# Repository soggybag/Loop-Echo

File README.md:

# Loop Echo (working name)

A single-PT2399 delay with an **effects loop in the feedback path**:
- only the repeats circulate through the loop;
- the first echo is clean, and each later echo goes through the external effect again: fuzz degrades, a filter re-voices, a pitch shifter cascades;
- delay-time modulation (RATE, DEPTH);
- true bypass, plus a **LOOP footswitch** that switches the effects loop in or out of the repeats.

The PT2399 network is taken from your Small Time (`~/Documents/eagle/projects/Small Time/`, 2022), without its tails JFET.

- **Schematic:** [docs/LoopEcho_schematic.pdf](docs/LoopEcho_schematic.pdf), generated by `scripts/build_loopecho.py`. ERC 0.
- **Board:** `LoopEcho.kicad_pcb`, from `scripts/buildpcb_loopecho.py` (don't re-run it after editing the board in KiCad).
- **Notes:** [docs/Design Notes.md](docs/Design%20Notes.md).

**Controls (v1.0):** TIME (B50k), REPEAT (B10k), MIX (B10k), RATE (B1M), DEPTH (B100k), **TONE (B50k)**: six knobs.

**Jacks (v1.0):** all board-mounted on the top wall of a **1590BB (landscape)**, outside view left → right: **OUT · RETURN · DC · SEND · IN** (Tayda A-6728 PJ-646F stereo switched jacks, A-4118 DC jack). RETURN is switched: with no plug, its tip switch ties RETURN to SEND, so the loop closes internally and it's a normal delay.

**Status:** **v1.0 SMD schematic (2026-10-25)**, to be ordered as a prototype (not breadboarded; the PT2399 network is proven in Small Time). ERC 0. All SMD parts are JLC basic except the PT2399-SN (C126407). Changes from v0.1: SEND / switched RETURN instead of the TRS insert; **TONE** in the feedback path (B50k + 2k2 into 10n, ~7 kHz-300 Hz, on every repeat, loop or internal); LFO into the TIME / 2k7 node (even depth, Dragonfish) on an LM358; AMS1117-5.0; SS14; status LED + footswitch header. v0.1 generator kept as `scripts/build_loopecho_v0.1.py`. **Board (2026-10-25):** `LoopEcho.kicad_pcb`, 1590BB landscape, 100 × 83.5 mm, two footswitches (LOOP left, BYPASS right; a SwitchPCB v2 on each), routed (re-routed 2026-10-26: supply nets +9V / GND / +5V / VB / D1-A at 0.4 mm, signals 0.25 mm, 88 vias): DRC 0 errors / 0 unconnected, parity clean. Panel layout and drill notes in the Design Notes (*Board*). **Fab files (2026-10-26, after the re-route):** `production/` (gitignored: attach the zip to a GitHub Release): `LoopEcho.zip` (Gerbers + PTH/NPTH drill, slots included), `bom.csv` + `positions.csv` (75 SMD placements, top side only, 28 lines, all LCSC; only the PT2399 is an extended part), `LoopEcho_hand_solder.csv`. **In JLC's preview check U1 (PT2399) and U5 (SOT-223) rotation**; the op-amps carry FT Rotation Offset 270. Drilling: [enclosure/README.md](enclosure/README.md). Silk pass done 2026-10-26 (references clear of pads and other silk; Gerbers regenerated): the only DRC warnings left are the jack outlines running past the top edge (by design) and C13's reference touching U2's outline.

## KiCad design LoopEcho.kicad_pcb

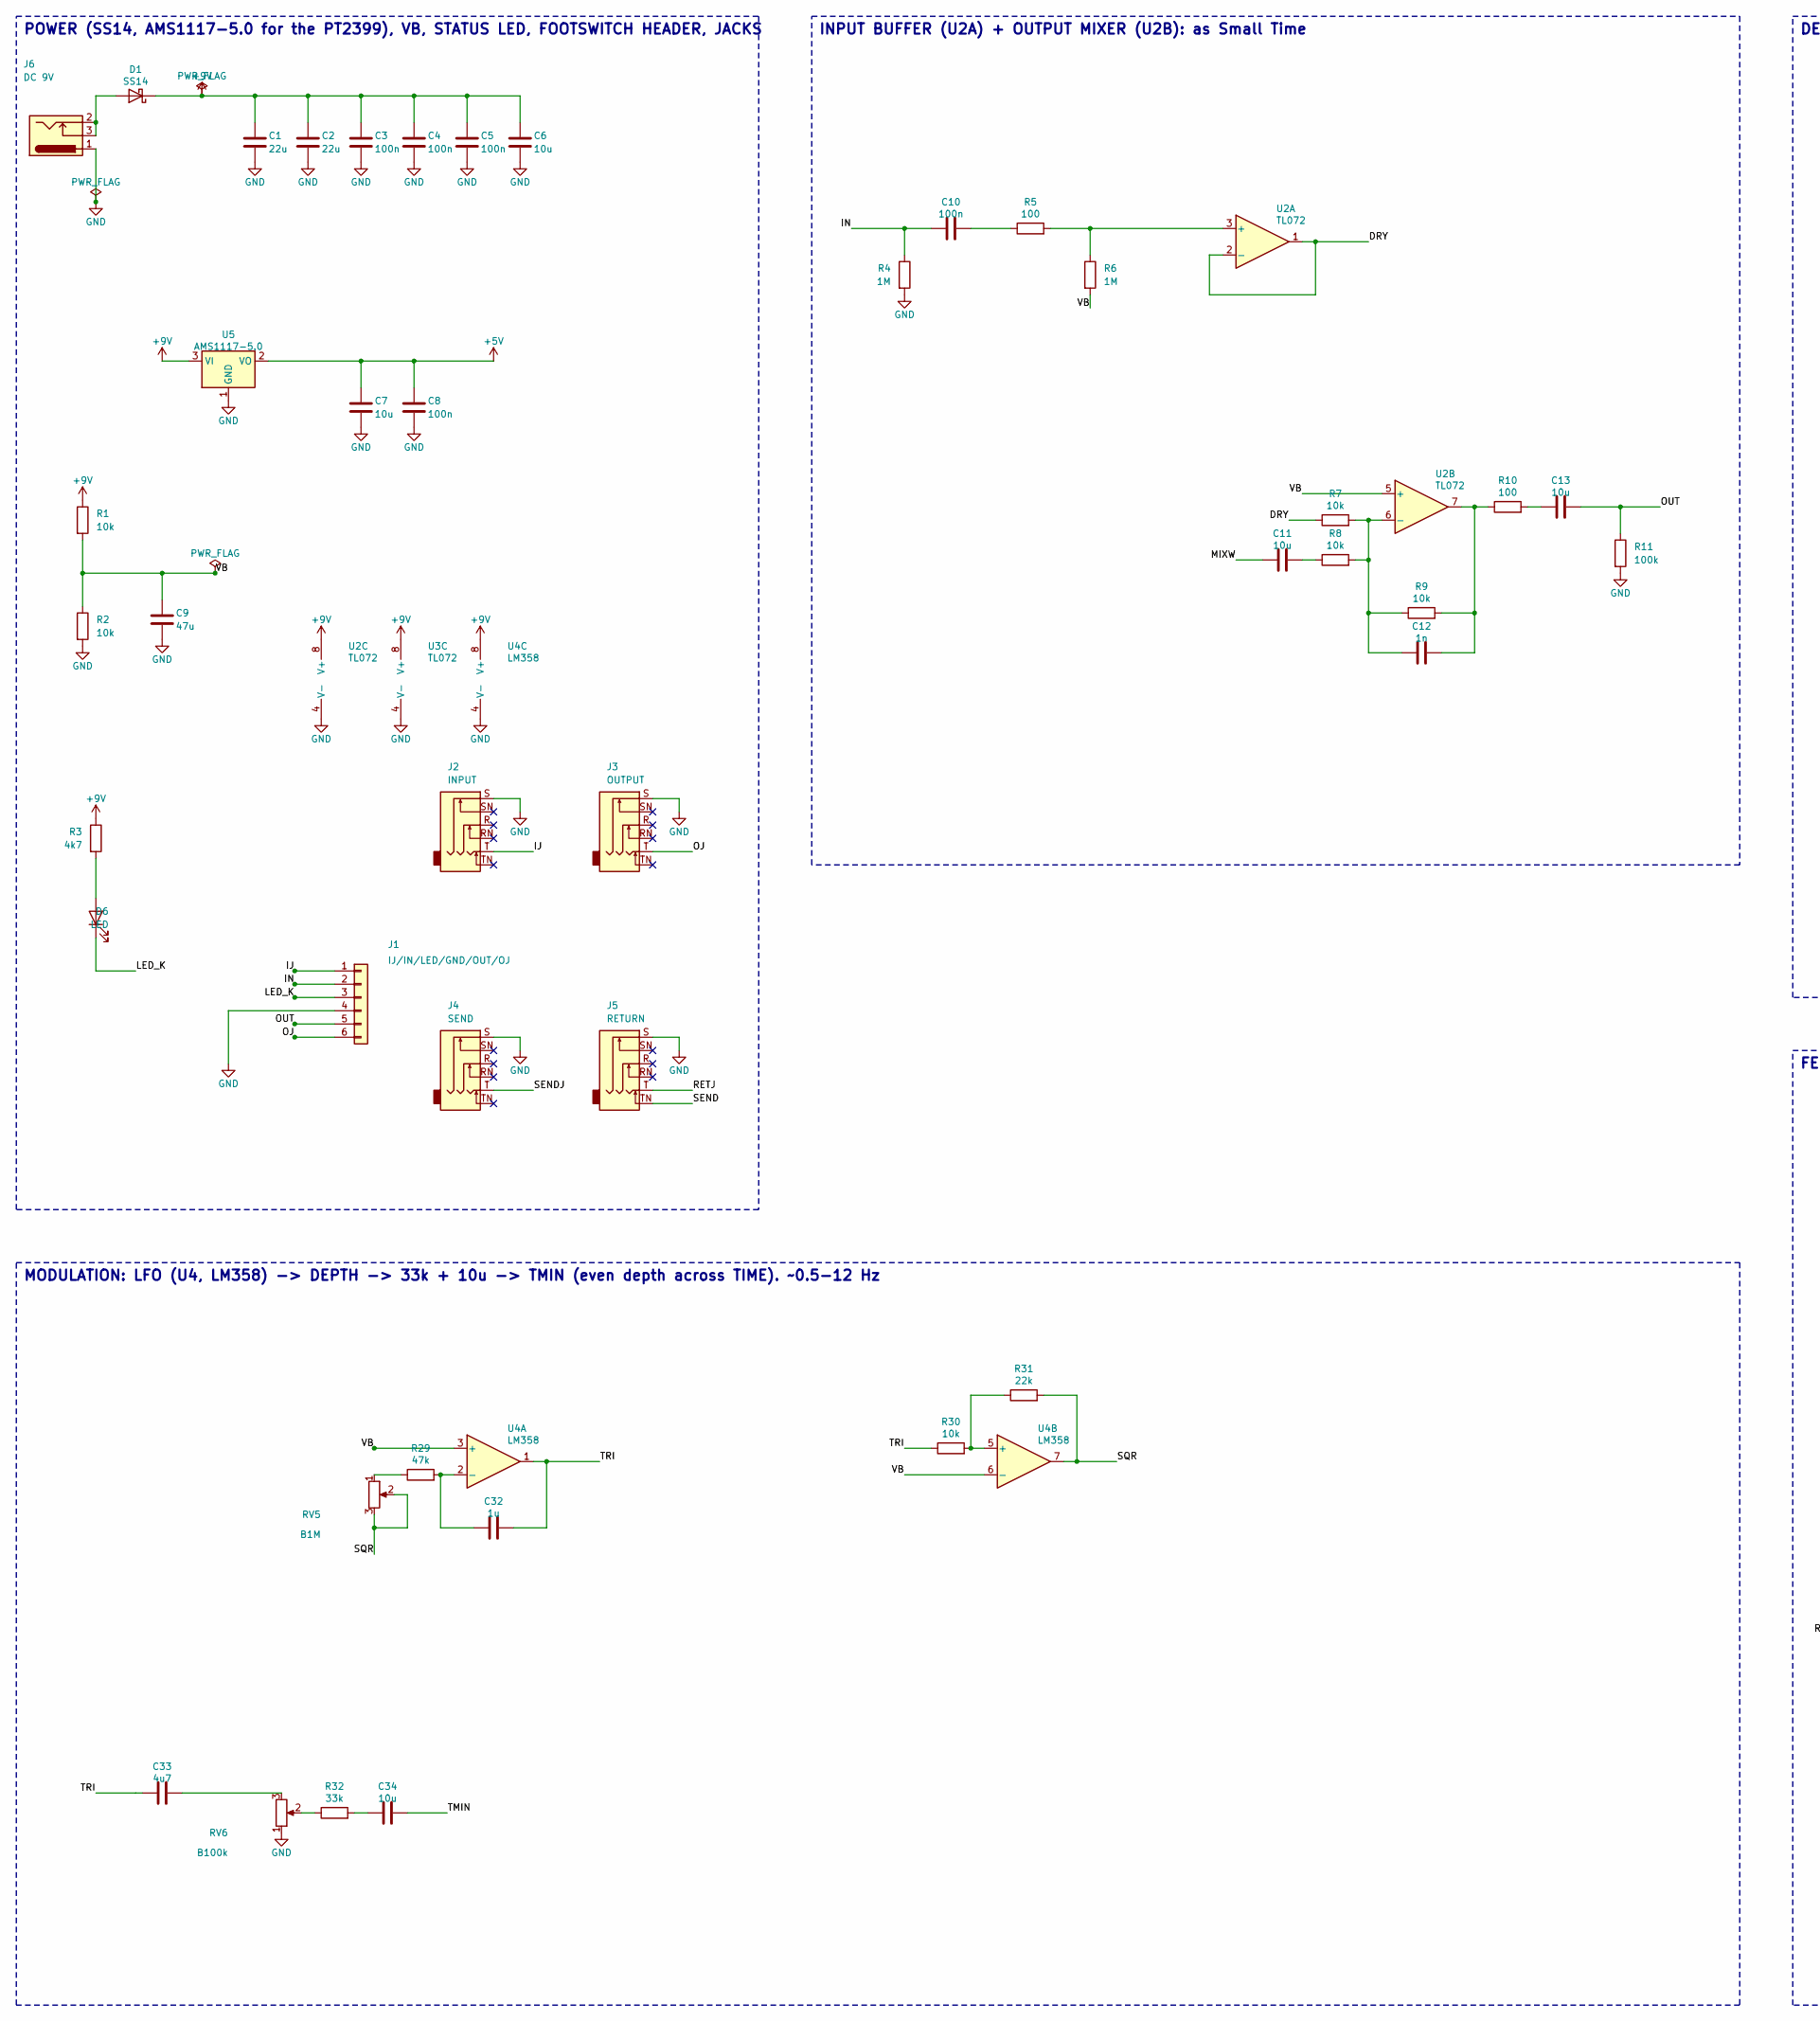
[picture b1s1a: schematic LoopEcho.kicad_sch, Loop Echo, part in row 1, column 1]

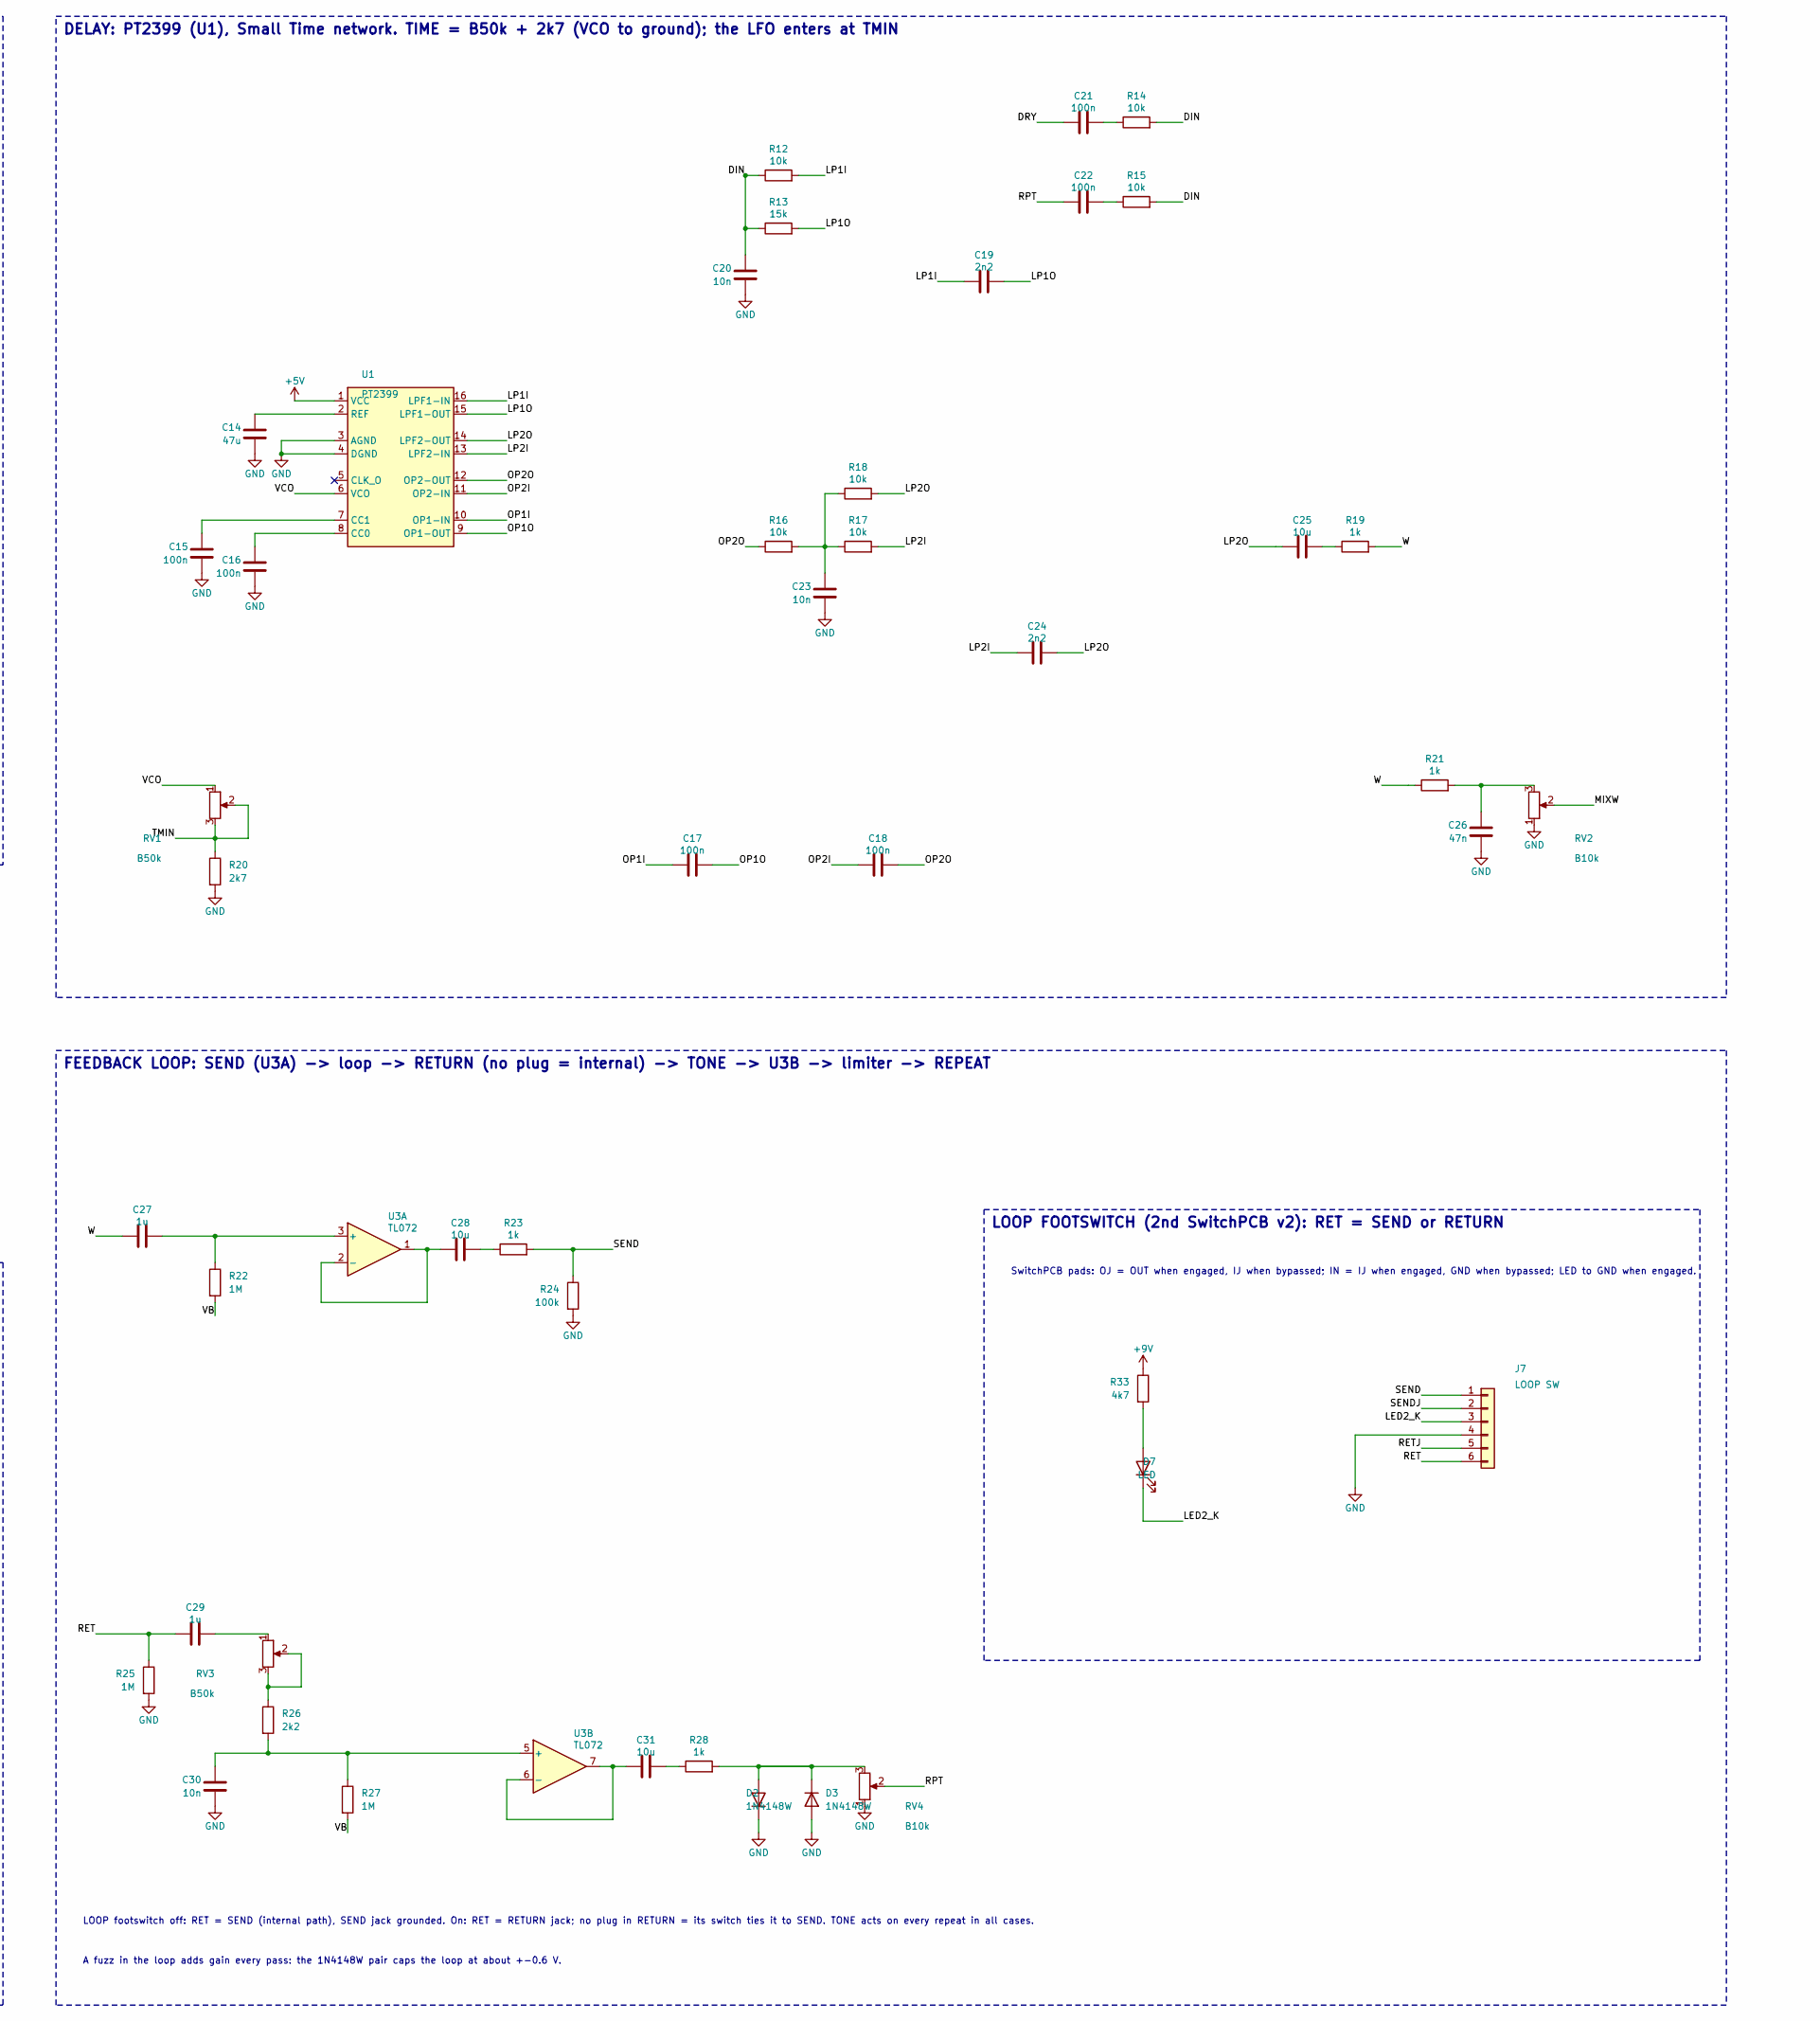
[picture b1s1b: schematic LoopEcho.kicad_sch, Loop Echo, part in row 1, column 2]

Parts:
C1, C2: 22u; C_0805_2012Metric_Pad1.18x1.45mm_HandSolder; LCSC C45783
C3, C4, C5, C8, C10, C15, C16, C17, C18, C21, C22: 100n; C_0805_2012Metric_Pad1.18x1.45mm_HandSolder; LCSC C49678
C6, C7, C11, C13, C25, C28, C31, C34: 10u; C_0805_2012Metric_Pad1.18x1.45mm_HandSolder; LCSC C15850
C9, C14: 47u; C_1206_3216Metric_Pad1.33x1.80mm_HandSolder; LCSC C96123
C12: 1n; C_0805_2012Metric_Pad1.18x1.45mm_HandSolder; LCSC C46653
C19, C24: 2n2; C_0805_2012Metric_Pad1.18x1.45mm_HandSolder; LCSC C28260
C20, C23, C30: 10n; C_0805_2012Metric_Pad1.18x1.45mm_HandSolder; LCSC C1710
C26: 47n; C_0805_2012Metric_Pad1.18x1.45mm_HandSolder; LCSC C53134
C27, C29, C32: 1u; C_0805_2012Metric_Pad1.18x1.45mm_HandSolder; LCSC C28323
C33: 4u7; C_0805_2012Metric_Pad1.18x1.45mm_HandSolder; LCSC C1779
D1: SS14; D_SMA; LCSC C2480
D2, D3: 1N4148W; D_SOD-123; LCSC C81598
D6, D7: LED; LED_D3.0mm
J1: IJ/IN/LED/GND/OUT/OJ; PinHeader_1x06_P2.54mm_Vertical
J2: INPUT; Jack_6.35mm_PJ-646F_Horizontal
J3: OUTPUT; Jack_6.35mm_PJ-646F_Horizontal
J4: SEND; Jack_6.35mm_PJ-646F_Horizontal
J5: RETURN; Jack_6.35mm_PJ-646F_Horizontal
J6: DC 9V; DC_Jack_2.1mm_A-4118_Horizontal
J7: LOOP SW; PinHeader_1x06_P2.54mm_Vertical
R1, R2, R7, R8, R9, R12, R14, R15, R16, R17, R18, R30: 10k; R_0805_2012Metric_Pad1.20x1.40mm_HandSolder; LCSC C17414
R3, R33: 4k7; R_0805_2012Metric_Pad1.20x1.40mm_HandSolder; LCSC C17673
R4, R6, R22, R25, R27: 1M; R_0805_2012Metric_Pad1.20x1.40mm_HandSolder; LCSC C17514
R5, R10: 100; R_0805_2012Metric_Pad1.20x1.40mm_HandSolder; LCSC C17408
R11, R24: 100k; R_0805_2012Metric_Pad1.20x1.40mm_HandSolder; LCSC C149504
R13: 15k; R_0805_2012Metric_Pad1.20x1.40mm_HandSolder; LCSC C17475
R19, R21, R23, R28: 1k; R_0805_2012Metric_Pad1.20x1.40mm_HandSolder; LCSC C17513
R20: 2k7; R_0805_2012Metric_Pad1.20x1.40mm_HandSolder; LCSC C17530
R26: 2k2; R_0805_2012Metric_Pad1.20x1.40mm_HandSolder; LCSC C17520
R29: 47k; R_0805_2012Metric_Pad1.20x1.40mm_HandSolder; LCSC C17713
R31: 22k; R_0805_2012Metric_Pad1.20x1.40mm_HandSolder; LCSC C17560
R32: 33k; R_0805_2012Metric_Pad1.20x1.40mm_HandSolder; LCSC C17633
RV1, RV3: B50k; Potentiometer_Alpha_RD901F-40-00D_Single_Vertical
RV2, RV4: B10k; Potentiometer_Alpha_RD901F-40-00D_Single_Vertical
RV5: B1M; Potentiometer_Alpha_RD901F-40-00D_Single_Vertical
RV6: B100k; Potentiometer_Alpha_RD901F-40-00D_Single_Vertical
U1: PT2399; SOIC-16_3.9x9.9mm_P1.27mm; LCSC C126407
U2, U3: TL072; SOIC-8_3.9x4.9mm_P1.27mm; LCSC C6961
U4: LM358; SOIC-8_3.9x4.9mm_P1.27mm; LCSC C7950
U5: AMS1117-5.0; SOT-223-3_TabPin2; LCSC C6187

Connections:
+5V: C7.1, C8.1, U1.1 (VCC), U5.2 (VO)
/DIN: C20.1, R12.1, R13.1, R14.2, R15.2
/DRY: C21.1, R7.1, U2.1, U2.2 (-)
/IJ: J1.1, J2.T
/IN: C10.1, J1.2, R4.1
/LED2_K: D7.1 (K), J7.3
/LED_K: D6.1 (K), J1.3
/LP1I: C19.1, R12.2, U1.16 (LPF1-IN)
/LP1O: C19.2, R13.2, U1.15 (LPF1-OUT)
/LP2I: C24.1, R17.2, U1.13 (LPF2-IN)
/LP2O: C24.2, C25.1, R18.2, U1.14 (LPF2-OUT)
/MIXW: C11.1, RV2.2
/OJ: J1.6, J3.T
/OP1I: C17.1, U1.10 (OP1-IN)
/OP1O: C17.2, U1.9 (OP1-OUT)
/OP2I: C18.1, U1.11 (OP2-IN)
/OP2O: C18.2, R16.1, U1.12 (OP2-OUT)
/OUT: C13.2, J1.5, R11.1
/RET: C29.1, J7.6, R25.1
/RETJ: J5.T, J7.5
/RPT: C22.1, RV4.2
/SEND: J5.TN, J7.1, R23.2, R24.1
/SENDJ: J4.T, J7.2
/SQR: R31.2, RV5.2, RV5.3, U4.7
/TMIN: C34.2, R20.1, RV1.2, RV1.3
/TRI: C32.2, C33.1, R30.1, U4.1
/VCO: RV1.1, U1.6 (VCO)
/W: C27.1, R19.2, R21.1
unnamed: C10.2, R5.1
unnamed: C11.2, R8.1
unnamed: C12.2, R9.2, R10.1, U2.7
unnamed: C13.1, R10.2
unnamed: C21.2, R14.1
unnamed: C22.2, R15.1
unnamed: C23.1, R16.2, R17.1, R18.1
unnamed: C25.2, R19.1
unnamed: C26.1, R21.2, RV2.3
unnamed: C28.2, R23.1
unnamed: C29.2, RV3.1
unnamed: C31.2, R28.1
unnamed: C33.2, RV6.3
unnamed: C34.1, R32.2
unnamed: D1.2 (A), J6.2, J6.3
unnamed: D2.2 (A), D3.1 (K), R28.2, RV4.3
unnamed: D6.2 (A), R3.2
unnamed: D7.2 (A), R33.2
unnamed: R26.1, RV3.2, RV3.3
unnamed: R29.1, RV5.1
unnamed: R32.1, RV6.2
unnamed: C16.1, U1.8 (CC0)
unnamed: C15.1, U1.7 (CC1)
unnamed: C14.1, U1.2 (REF)
unnamed: R5.2, R6.1, U2.3 (+)
unnamed: C12.1, R7.2, R8.2, R9.1, U2.6 (-)
unnamed: C27.2, R22.1, U3.3 (+)
unnamed: C28.1, U3.1, U3.2 (-)
unnamed: C30.1, R26.2, R27.1, U3.5 (+)
unnamed: C31.1, U3.6 (-), U3.7
unnamed: C32.1, R29.2, U4.2 (-)
unnamed: R30.2, R31.1, U4.5 (+)

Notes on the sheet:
POWER (SS14, AMS1117-5.0 for the PT2399), VB, STATUS LED, FOOTSWITCH HEADER, JACKS
INPUT BUFFER (U2A) + OUTPUT MIXER (U2B): as Small Time
DELAY: PT2399 (U1), Small Time network. TIME = B50k + 2k7 (VCO to ground); the LFO enters at TMIN
FEEDBACK LOOP: SEND (U3A) -> loop -> RETURN (no plug = internal) -> TONE -> U3B -> limiter -> REPEAT
LOOP footswitch off: RET = SEND (internal path), SEND jack grounded. On: RET = RETURN jack; no plug in RETURN = its switch ties it to SEND. TONE acts on every repeat in all cases.
A fuzz in the loop adds gain every pass: the 1N4148W pair caps the loop at about +-0.6 V.
MODULATION: LFO (U4, LM358) -> DEPTH -> 33k + 10u -> TMIN (even depth across TIME). ~0.5-12 Hz
LOOP FOOTSWITCH (2nd SwitchPCB v2): RET = SEND or RETURN
SwitchPCB pads: OJ = OUT when engaged, IJ when bypassed; IN = IJ when engaged, GND when bypassed; LED to GND when engaged.

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
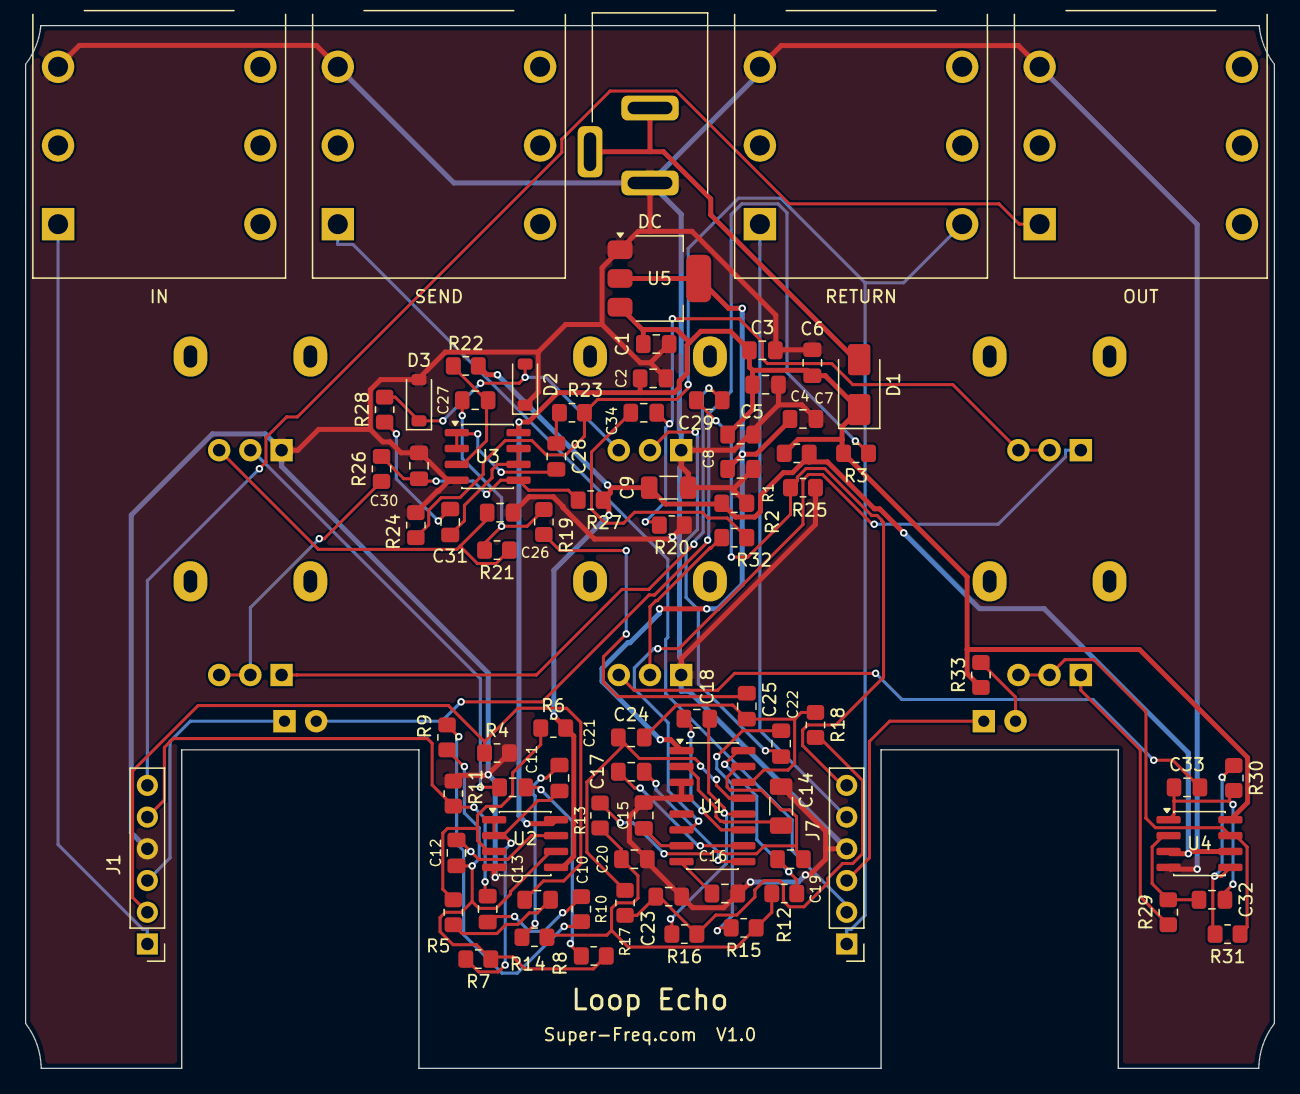
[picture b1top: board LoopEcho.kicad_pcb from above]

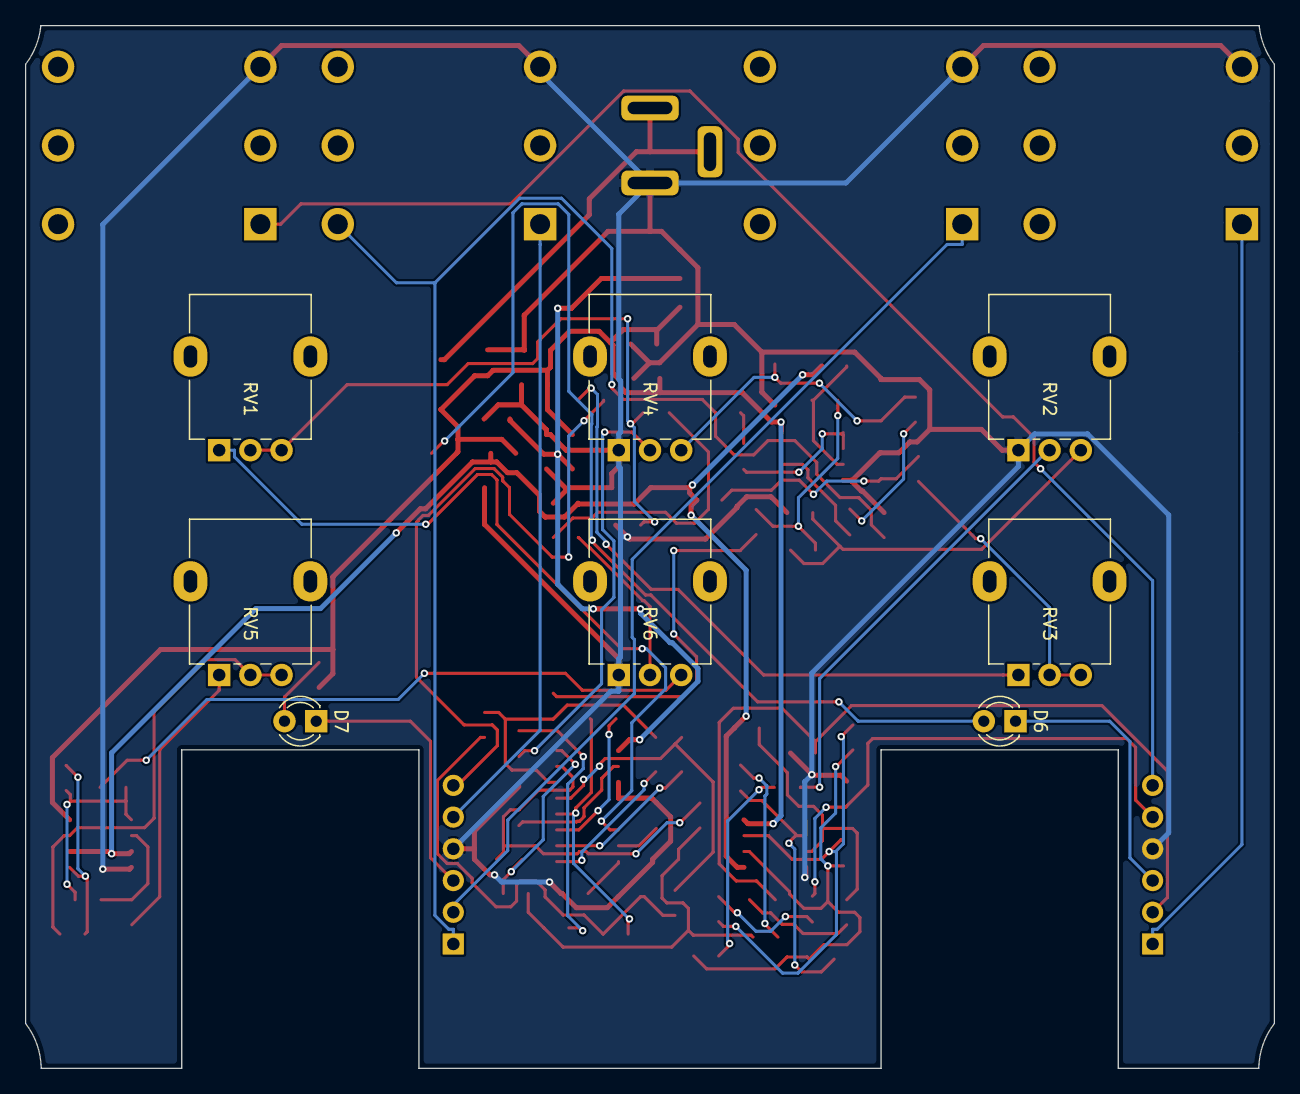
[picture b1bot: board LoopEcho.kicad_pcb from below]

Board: 2 copper layers, 100.0 x 83.5 mm, 90 parts (8 on the bottom side), 63 nets.

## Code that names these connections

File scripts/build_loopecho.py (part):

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repeat, and delay-time modulation. PT2399 network from the user's Small Time. Ordered as a prototype (not breadboarded).
v0.1 (breadboard, TRS insert) is kept as build_loopecho_v0.1.py.
  - U2A input buffer (DRY); U2B inverting mixer (DRY + MIX)
  - U1 PT2399-SN on its own 5 V (U5 AMS1117-5.0); TIME = B50k + 2k7 from VCO (pin 6) to ground (~50-600 ms)
  - wet (W) -> U3A SEND buffer -> SEND pad.  RETURN jack (switched): no plug -> its normal contact = SEND (internal path).
    RET -> 1u -> TONE (B50k + 2k2 into 10n: ~7 kHz .. 300 Hz, every repeat) -> U3B -> 1k + 1N4148W limiter -> REPEAT -> PT2399
  - LFO U4 (LM358: integrator + Schmitt, RATE 47k + B1M, 1u) -> DEPTH -> 33k + 10u -> TMIN (the TIME / 2k7 node):
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W(P(r, '2'), P('D6', '2')); W(P('D6', '1'), (g(10), g(78)), (g(13), g(78))); lab('LED_K', (g(13), g(78)))
s.part('J1', 'Connector_Generic', 'Conn_01x06', 'IJ/IN/LED/GND/OUT/OJ', g(30), g(80), 0, fp='Connector_PinHeader_2.54mm:PinHeader_1x06_P2.54mm_Vertical',
       desc='To the SwitchPCB v2 (same order as its pads): 1 IJ, 2 IN, 3 LED_K, 4 GND, 5 OUT, 6 OJ', text=((g(32), g(76)), (g(32), g(77.2)), 'left'), bom=False)
for pin, net in (('1', 'IJ'), ('2', 'IN'), ('3', 'LED_K'), ('5', 'OUT'), ('6', 'OJ')):
    q = P('J1', pin); W(q, (q[0] - g(3), q[1])); lab(net, (q[0] - g(3), q[1]), 'l')
q = P('J1', '4'); W(q, (q[0] - g(8), q[1]), (q[0] - g(8), q[1] + g(4))); GND((q[0] - g(8), q[1] + g(4)))
# board-mounted jacks (PJ-646F stereo switched; outside view of the top wall: OUT  RETURN  DC  SEND  IN)
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for pin, dx in (('7', 10), ('8', 6)):
    q = P('U1', pin); cc = (q[0] - g(dx), q[1]); W(q, cc)
    c = Cv('100n', cc[0], cc[1] + g(1) + 3.81, side='l', d=f'Compander (pin {pin})'); W(cc, P(c, '1')); GND(P(c, '2'))
for pin, name in (('9', 'OP1O'), ('10', 'OP1I'), ('11', 'OP2I'), ('12', 'OP2O'), ('13', 'LP2I'), ('14', 'LP2O'), ('15', 'LP1O'), ('16', 'LP1I')):
    lab_at(P('U1', pin), name, 3)
for a, b, x in (('OP1I', 'OP1O', 186), ('OP2I', 'OP2O', 200)):
    c = Ch('100n', g(x), g(70), d=f'{a}-{b} (PT2399 integrator)')
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W(P('R33', '2'), P('D7', '2')); W(P('D7', '1'), (g(220), g(119.5)), (g(223), g(119.5))); lab('LED2_K', (g(223), g(119.5)))
s.part('J7', 'Connector_Generic', 'Conn_01x06', 'LOOP SW', g(246), g(112), 0, fp='Connector_PinHeader_2.54mm:PinHeader_1x06_P2.54mm_Vertical',
       desc='To the LOOP SwitchPCB v2: 1 IJ = SEND, 2 IN = SEND jack, 3 LED2_K, 4 GND, 5 OUT = RETURN jack, 6 OJ = RET', text=((g(248), g(108)), (g(248), g(109.2)), 'left'), bom=False)
for pin, net in (('1', 'SEND'), ('2', 'SENDJ'), ('3', 'LED2_K'), ('5', 'RETJ'), ('6', 'RET')):
    q = P('J7', pin); W(q, (q[0] - g(3), q[1])); lab(net, (q[0] - g(3), q[1]), 'l')
q = P('J7', '4'); W(q, (q[0] - g(8), q[1]), (q[0] - g(8), q[1] + g(4))); GND((q[0] - g(8), q[1] + g(4)))

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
